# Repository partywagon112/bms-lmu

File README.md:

# Battery Management System - Local Measurement Unit

Final Year Research Project (FYRP) by Ethan Suter and Patrick Curtain to design a battery management system for an electric solar vehicle.

The Local Measurement Unit (LMU) is used to relay information about the cells to the Central Management Unit (CMU) that will they respond with balance target values for the LMU to act on. The LMU interconnects to the cell stack with the use of a terminal board, contained within the same repository. 

The LMU features an LTC6811 to monitor the cells, with two LTC3300 to actively balance the stack. These connect through multiple isolated SPI interfaces, to a microcontroller that is used to preprocess the data into a simpler form for the CMU to decypher.

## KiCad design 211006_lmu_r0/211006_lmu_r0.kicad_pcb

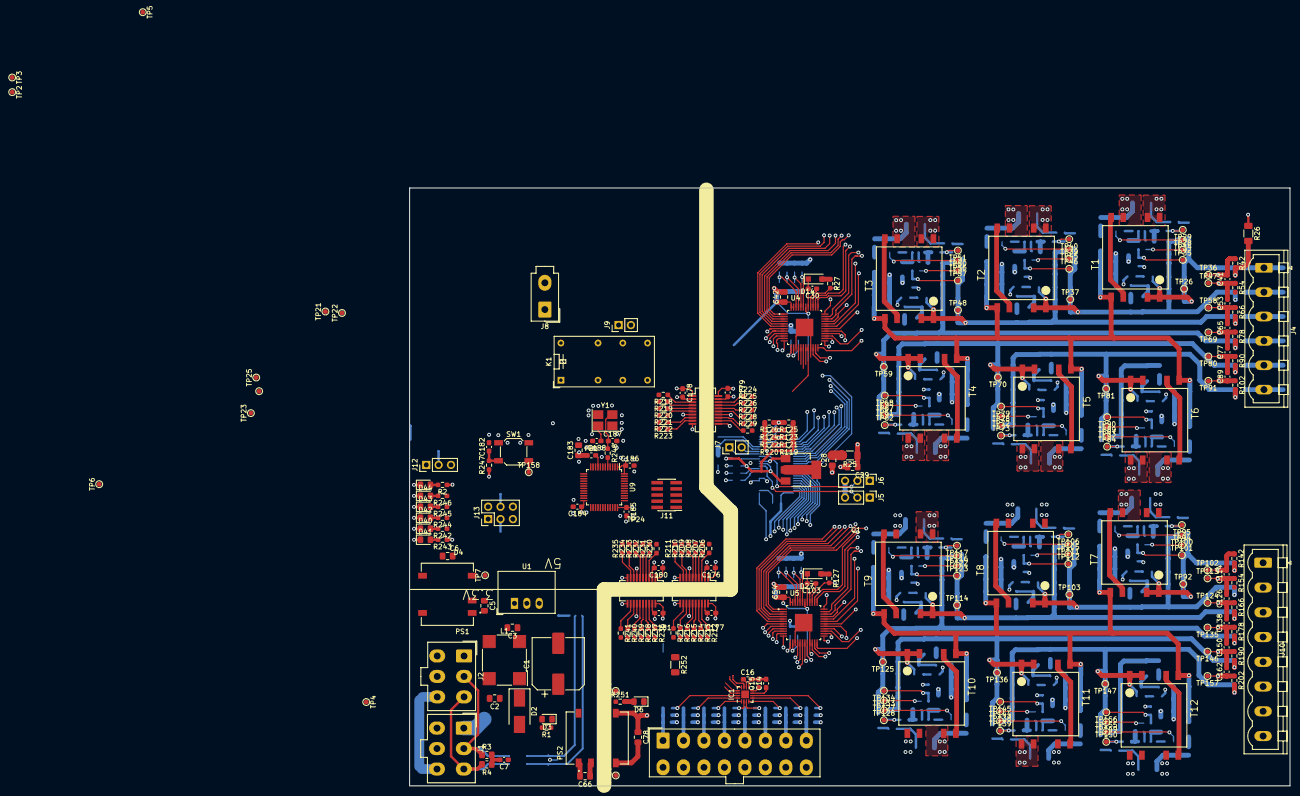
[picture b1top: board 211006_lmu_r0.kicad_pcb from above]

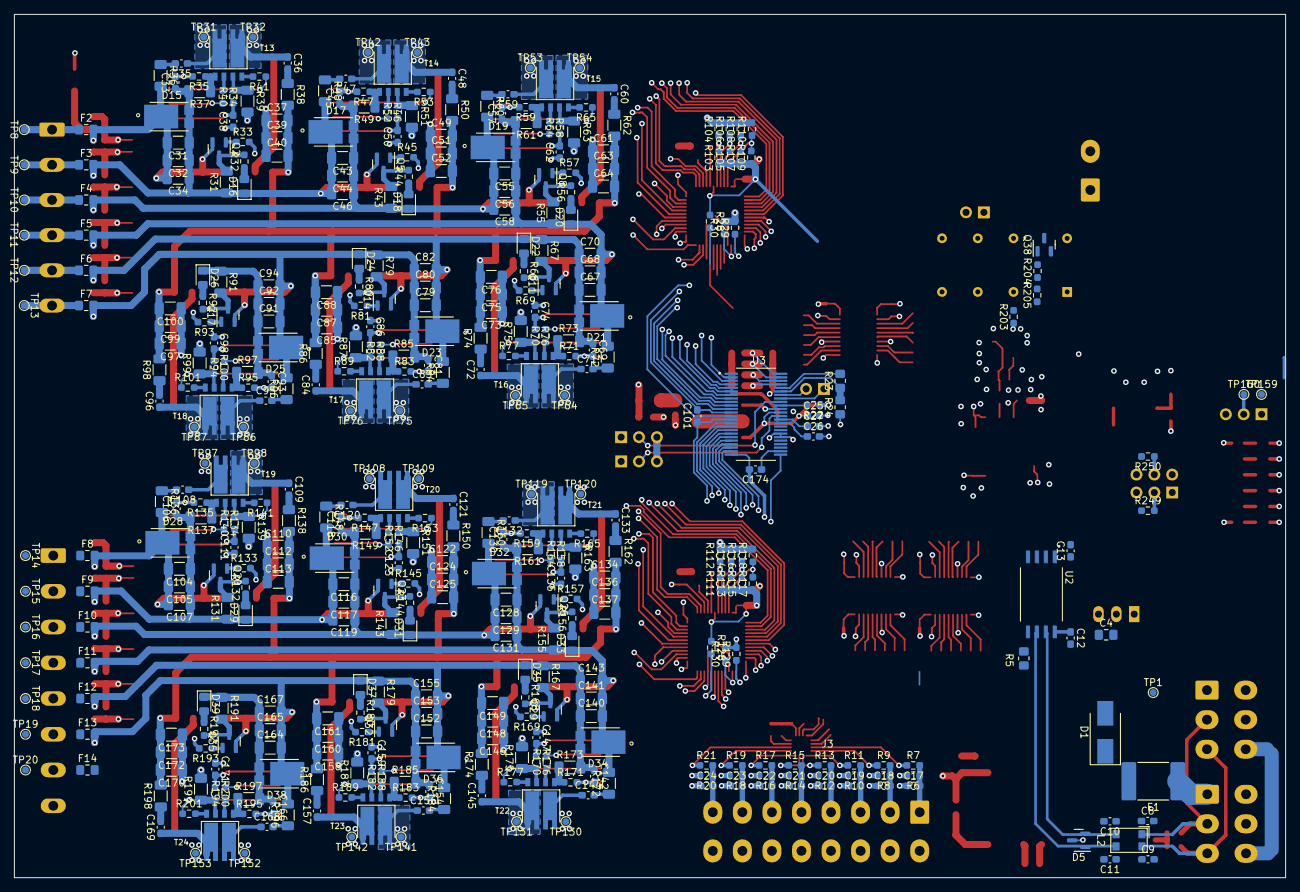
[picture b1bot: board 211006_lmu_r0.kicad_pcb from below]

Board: 4 copper layers, 180.7 x 122.7 mm, 678 parts (427 on the bottom side), 408 nets.

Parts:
C1: 220uF; CP_Elec_10x12.5
C2, C3: 10uF; C_0805_2012Metric_Pad1.18x1.45mm_HandSolder
C4, C6, C78: 22uF; C_0805_2012Metric_Pad1.18x1.45mm_HandSolder
C5, C28, C29, C66: 100nF; C_0805_2012Metric_Pad1.18x1.45mm_HandSolder
C7, C17, C18, C19, C20, C21, C22, C23, C24, C41, C53, C65, C77, C89, C101, C114, C126, C138, C150, C162, C174, C182: 10nF; C_0603_1608Metric_Pad1.08x0.95mm_HandSolder
C8, C9, C10, C11: DNP 10pF; C_0603_1608Metric_Pad1.08x0.95mm_HandSolder
C12, C13, C25, C26, C27, C30, C103, C176, C177, C178, C179, C180, C181, C184, C185, C186: 100nF; C_0603_1608Metric_Pad1.08x0.95mm_HandSolder
C14, C15, C16: 1uF; C_0603_1608Metric_Pad1.08x0.95mm_HandSolder
C31, C32, C34, C37, C39, C40, C43, C44, C46, C49, C51, C52, C55, C56, C58, C61, C63, C64, C67, C68, C70, C73, C75, C76, C79, C80, C82, C85, C87, C88, C91, C92, C94, C97, C99, C100, C104, C105, C107, C110, C112, C113, C116, C117, C119, C122, C124, C125, C128, C129, C131, C134, C136, C137, C140, C141, C143, C146, C148, C149, C152, C153, C155, C158, C160, C161, C164, C165, C167, C170, C172, C173: 100uF; C_1206_3216Metric_Pad1.33x1.80mm_HandSolder
C33, C45, C57, C69, C81, C93, C106, C118, C130, C142, C154, C166: 2.2nF; C_0603_1608Metric_Pad1.08x0.95mm_HandSolder
C35, C36, C38, C47, C48, C50, C59, C60, C62, C71, C72, C74, C83, C84, C86, C95, C96, C98, C108, C109, C111, C120, C121, C123, C132, C133, C135, C144, C145, C147, C156, C157, C159, C168, C169, C171: 470pF; C_0603_1608Metric_Pad1.08x0.95mm_HandSolder
C42, C54: 1u; C_0805_2012Metric_Pad1.18x1.45mm_HandSolder
C183: 1uF; C_0805_2012Metric_Pad1.18x1.45mm_HandSolder
C187, C188: 22p; C_0603_1608Metric_Pad1.08x0.95mm_HandSolder
D1: 1SMB5942B-13; D_SMB_Handsoldering
D2: SD560BTR; D_SMB_Handsoldering
D3, D4, D6, D16, D18, D20, D22, D24, D26, D29, D31, D33, D35, D37, D39, D41: LED (Red); LED_0805_2012Metric_Pad1.15x1.40mm_HandSolder
D5: NUP2105L; SOT-23
D14, D27: CMMSH2-40; D_SOD-123F
D15, D17, D19, D21, D23, D25, D28, D30, D32, D34, D36, D38: SDT15H100P5-7; DIO_SBR10U200P5-13
D40, D42: LED (Blue); LED_0805_2012Metric_Pad1.15x1.40mm_HandSolder
D43, D44: LED (Orange); LED_0805_2012Metric_Pad1.15x1.40mm_HandSolder
F1: Polyfuse 1A; Fuse_2920_7451Metric_Pad2.10x5.45mm_HandSolder
F2, F3, F4, F5, F6, F7, F8, F9, F10, F11, F12, F13, F14: Fuse; Fuse_0805_2012Metric_Pad1.15x1.40mm_HandSolder
FB1: Ferrite Bead; L_0603_1608Metric_Pad1.05x0.95mm_HandSolder
IC1: ADS7028QRTERQ1; WQFN-16-1EP_3x3mm_P0.5mm_EP1.6x1.6mm
J1, J2: Conn_02x03_Odd_Even; Molex_Mini-Fit_Jr_5566-06A_2x03_P4.20mm_Vertical
J3: Conn_02x08_Odd_Even; Molex_Mini-Fit_Jr_5566-16A_2x08_P4.20mm_Vertical
J4: UPPER_BANK; PhoenixContact_MSTBVA_2,5_6-G_1x06_P5.00mm_Vertical
J5, J6, J12: Conn_01x03; PinHeader_1x03_P2.54mm_Vertical
J7, J9: Conn_01x02; PinHeader_1x02_P2.54mm_Vertical
J8: Conn_01x02; Molex_Mini-Fit_Jr_5566-02A_2x01_P4.20mm_Vertical
J10: LOWER_BANK; PhoenixContact_MSTBVA_2,5_8-G-5,08_1x08_P5.08mm_Vertical
J11: Conn_ARM_JTAG_SWD_10; PinHeader_2x05_P1.27mm_Vertical_SMD
J13: Conn_02x03_Odd_Even; PinHeader_2x03_P2.54mm_Vertical
K1: G5V-2 DC-3; Relay_DPDT_Omron_G5V-2
L1: 744272121; L_CommonModeChoke_Wuerth_WE-SL5
L2: 0ZCF0100AF2A; L_CommonModeChoke_Coilcraft_1812CAN
PS1: R2S-053.3; CONV_R2S-053.3
PS2: R2S-0505; CONV_R2S-0505
Q1: CZT5551; SOT-223-3_TabPin2
Q2, Q5, Q8, Q11, Q14, Q17, Q20, Q23, Q26, Q29, Q32, Q35: BSS308PE; SOT-23
Q38: BC817; SOT-23
R1, R2, R242, R243, R244, R245, R246, R251: 2.2kR; R_0603_1608Metric_Pad0.98x0.95mm_HandSolder
R3, R4: 60R; R_0805_2012Metric_Pad1.20x1.40mm_HandSolder
R5: 0R; R_0805_2012Metric_Pad1.20x1.40mm_HandSolder
R6, R8, R10, R12, R14, R16, R18, R20, R204: 10kR; R_0603_1608Metric_Pad0.98x0.95mm_HandSolder
R7, R9, R11, R13, R15, R17, R19, R21, R203, R205, R206, R207, R208, R209, R210, R211, R212, R213, R214, R215, R216, R217, R218, R219, R220, R221, R222, R223, R224, R225, R226, R227, R228, R229, R230, R231, R232, R233, R234, R235, R236, R237, R238, R239, R240, R241, R247, R249, R250: 50kR; R_0603_1608Metric_Pad0.98x0.95mm_HandSolder
R22, R28, R128: 1MR; R_0603_1608Metric_Pad0.98x0.95mm_HandSolder
R23, R24: DNP; R_0805_2012Metric_Pad1.20x1.40mm_HandSolder
R25, R26: 100R; R_1206_3216Metric_Pad1.30x1.75mm_HandSolder
R27, R127: 6.81R; R_0603_1608Metric_Pad0.98x0.95mm_HandSolder
R29, R129: 23.7kR; R_0603_1608Metric_Pad0.98x0.95mm_HandSolder
R30, R130: 33.2kR; R_0603_1608Metric_Pad0.98x0.95mm_HandSolder
R31, R43, R55, R67, R79, R91, R131, R143, R155, R167, R179, R191: 330R; R_1206_3216Metric_Pad1.30x1.75mm_HandSolder
R32, R44, R56, R68, R80, R92, R132, R144, R156, R168, R180, R192: 470R; R_0603_1608Metric_Pad0.98x0.95mm_HandSolder
R33, R45, R57, R69, R81, R93, R133, R145, R157, R169, R181, R193: 3.3kR; R_0603_1608Metric_Pad0.98x0.95mm_HandSolder
R34, R41, R46, R53, R58, R65, R70, R77, R82, R89, R94, R101, R134, R141, R146, R153, R158, R165, R170, R177, R182, R189, R194, R201: 5.1R; R_0603_1608Metric_Pad0.98x0.95mm_HandSolder
R35, R40, R47, R52, R59, R64, R71, R76, R83, R88, R95, R100, R135, R140, R147, R152, R159, R164, R171, R176, R183, R188, R195, R200: 20R; R_0603_1608Metric_Pad0.98x0.95mm_HandSolder
R36, R38, R48, R50, R60, R62, R72, R74, R84, R86, R96, R98, R136, R138, R148, R150, R160, R162, R172, R174, R184, R186, R196, R198: 20R; R_1206_3216Metric_Pad1.30x1.75mm_HandSolder
R37, R39, R49, R51, R61, R63, R73, R75, R85, R87, R97, R99, R137, R139, R149, R151, R161, R163, R173, R175, R185, R187, R197, R199: 25mR; R_1206_3216Metric_Pad1.30x1.75mm_HandSolder
R42, R54, R66, R78, R90, R102, R142, R154, R166, R178, R190, R202: 100R; R_0603_1608Metric_Pad0.98x0.95mm_HandSolder
R103, R104, R105, R106, R107, R108, R109, R110, R111, R112, R113, R114, R115, R116, R117, R118, R119, R120, R121, R122, R123, R124, R125, R126: DNP 50k; R_0603_1608Metric_Pad0.98x0.95mm_HandSolder
R248: 0; R_0603_1608Metric_Pad0.98x0.95mm_HandSolder
R252: 0R DNP; R_1206_3216Metric_Pad1.30x1.75mm_HandSolder
SW1: SW_Push; SW_SPST_SKQG_WithStem
T1, T2, T3, T4, T5, T6, T7, T8, T9, T10, T11, T12: 750312504; EP13_SMT_H_8PIN_(750312504)
T13, T14, T15, T16, T17, T18, T19, T20, T21, T22, T23, T24: BUK9K13-60EX; SOT1205
TP1, TP2, TP3, TP4, TP5, TP6, TP7, TP8, TP9, TP10, TP11, TP12, TP13, TP14, TP15, TP16, TP17, TP18, TP19, TP20, TP21, TP22, TP23, TP24, TP25, TP26, TP28, TP29, TP30, TP31, TP32, TP33, TP34, TP35, TP36, TP37, TP39, TP40, TP42, TP43, TP45, TP46, TP47, TP48, TP50, TP51, TP53, TP54, TP56, TP57, TP58, TP59, TP61, TP62, TP64, TP65, TP67, TP68, TP69, TP70, TP72, TP73, TP75, TP76, TP78, TP79, TP80, TP81, TP83, TP84, TP86, TP87, TP89, TP90, TP91, TP92, TP94, TP95, TP97, TP98, TP100, TP101, TP102, TP103, TP105, TP106, TP108, TP109, TP111, TP112, TP113, TP114, TP116, TP117, TP119, TP120, TP122, TP123, TP124, TP125, TP127, TP128, TP130, TP131, TP133, TP134, TP135, TP136, TP138, TP139, TP141, TP142, TP144, TP145, TP146, TP147, TP149, TP150, TP152, TP153, TP155, TP156, TP157, TP158, TP159, TP160: TestPoint; TestPoint_Pad_D1.0mm
U1: R-78C5.0-1.0; Converter_DCDC_RECOM_R-78E-0.5_THT
U2: ISO1042DWVR; SOIC127P1150X280-8N
U3: LTC6811HG-2#PBF; SOP50P780X200-48N
U4, U5: LTC3300ILXE-2#PBF; QFP50P900X900X160-49N
U6, U7, U8: ADuM7641A; QSOP-20_3.9x8.7mm_P0.635mm
U9: STM32F103C8Tx; LQFP-48_7x7mm_P0.5mm
Y1: Crystal_GND24; Crystal_SMD_3225-4Pin_3.2x2.5mm_HandSoldering

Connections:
+3V3_ISO: C6.1, C13.1, C176.1, C178.1, C180.1, C183.1, C184.1, C185.1, C186.1, FB1.1, J11.1 (VTref), J13.1, J13.2, K1.1, K1.8, PS1.5 (+VOUT), R2.1, R243.1, R247.1, TP6.1, U2.1 (VCC1), U6.1 (VDD1A), U6.7 (VDD1B), U7.1 (VDD1A), U7.7 (VDD1B), U8.1 (VDD1A), U8.7 (VDD1B), U9.1 (VBAT), U9.24 (VDD), U9.36 (VDD), U9.48 (VDD)
+5V: C4.1, C5.1, C12.1, C66.1, PS1.2 (+VIN), PS2.2 (+VIN), R1.1, U1.3 (OUT), U2.8 (VCC2)
+5V_HV: C16.1, C78.1, C177.1, IC1.10 (DVDD), PS2.5 (+VOUT), R6.2, R8.2, R10.2, R12.2, R14.2, R16.2, R18.2, R20.2, R251.1, R252.2, TP30.1, U6.14 (VDD2B), U6.20 (VDD2A)
/Balance Interface/C0: C174.1, U3.26 (C0)
/Balance Interface/C1: C162.1, C174.2, R202.1, TP157.1, U3.24 (C1), U5.24 (C1)
/Balance Interface/C2: C150.1, C162.2, R190.1, TP146.1, U3.22 (C2), U5.27 (C2)
/Balance Interface/C3: C138.1, C150.2, R178.1, TP135.1, U3.20 (C3), U5.30 (C3)
/Balance Interface/C4: C126.1, C138.2, R166.1, TP124.1, U3.18 (C4), U5.33 (C4)
/Balance Interface/C5: C114.1, C126.2, R154.1, TP113.1, U3.16 (C5), U5.36 (C5)
/Balance Interface/C6: C101.1, C114.2, R127.2, R142.1, TP102.1, U3.14 (C6), U5.39 (C6)
/Balance Interface/C7: C89.1, C101.2, R102.1, TP91.1, U3.12 (C7), U4.24 (C1)
/Balance Interface/C8: C77.1, C89.2, R90.1, TP80.1, U3.10 (C8), U4.27 (C2)
/Balance Interface/C9: C65.1, C77.2, R78.1, TP69.1, U3.8 (C9), U4.30 (C3)
/Balance Interface/C10: C53.1, C65.2, R66.1, TP58.1, U3.6 (C10), U4.33 (C4)
/Balance Interface/C11: C41.1, C53.2, R54.1, TP47.1, U3.4 (C11), U4.36 (C5)
/Balance Interface/C12: C41.2, R27.2, R42.1, TP36.1, U3.2 (C12), U4.39 (C6)
/Balance Interface/CS: J7.1, R213.2, U3.41 (CSB/IMA)
/Balance Interface/DRIVE: Q1.1 (B), TP24.1, U3.38 (DRIVE)
/Balance Interface/DTEN: J5.2, U3.36 (DTEN)
/Balance Interface/IBIAS: IC1.12 (SDO), R23.2, R216.2, TP21.1, U3.44 (SDO/IBIAS)
/Balance Interface/ICMP: IC1.14 (SDI), R23.1, R24.2, R217.2, TP22.1, U3.43 (SDI/ICMP)
/Balance Interface/ISOMD: J6.2, U3.40 (ISOMD)
/Balance Interface/LOWER_ADDRESS/A0: R111.2, R112.1, U5.43 (A0)
/Balance Interface/LOWER_ADDRESS/A1: R113.2, R114.1, U5.44 (A1)
/Balance Interface/LOWER_ADDRESS/A2: R115.2, R116.1, U5.45 (A2)
/Balance Interface/LOWER_ADDRESS/A3: R117.2, R118.1, U5.46 (A3)
/Balance Interface/Lower Active Balance Group/ACTIVE_TAP1: C152.1, C153.1, C154.1, C155.1, C164.2, C165.2, C167.2, D36.2, D36.3, D37.1 (K), D38.1, F13.2, Q35.2 (S), R179.1, R185.2, R196.2, R202.2, T12.1, T12.2, TP147.1
/Balance Interface/Lower Active Balance Group/ACTIVE_TAP2: C140.1, C141.1, C142.1, C143.1, C152.2, C153.2, C155.2, D34.2, D34.3, D35.1 (K), D36.1, F12.2, Q32.2 (S), R167.1, R173.2, R184.2, R190.2, T11.1, T11.2, TP136.1
/Balance Interface/Lower Active Balance Group/ACTIVE_TAP3: C128.1, C129.1, C130.1, C131.1, C140.2, C141.2, C143.2, D32.2, D32.3, D33.1 (K), D34.1, F11.2, Q29.2 (S), R155.1, R161.2, R172.2, R178.2, T10.1, T10.2, TP125.1
/Balance Interface/Lower Active Balance Group/ACTIVE_TAP4: C116.1, C117.1, C118.1, C119.1, C128.2, C129.2, C131.2, D30.2, D30.3, D31.1 (K), D32.1, F10.2, Q26.2 (S), R143.1, R149.2, R160.2, R166.2, T9.1, T9.2, TP114.1
/Balance Interface/Lower Active Balance Group/ACTIVE_TAP5: C104.1, C105.1, C106.1, C107.1, C116.2, C117.2, C119.2, D28.2, D28.3, D29.1 (K), D30.1, F9.2, Q23.2 (S), R131.1, R137.2, R148.2, R154.2, T8.1, T8.2, TP103.1
/Balance Interface/Lower Active Balance Group/BOOST: C110.2, C112.2, C113.2, C122.2, C124.2, C125.2, C134.2, C136.2, C137.2, C146.2, C148.2, C149.2, C158.2, C160.2, C161.2, C170.2, C172.2, C173.2, R138.2, R150.2, R162.2, R174.2, R186.2, R198.2, T7.5, T8.5, T9.5, T10.5, T11.5, T12.5
/Balance Interface/Lower Active Balance Group/PG1: R194.2, TP149.1, U5.23 (G1P)
/Balance Interface/Lower Active Balance Group/PG2: R182.2, TP138.1, U5.26 (G2P)
/Balance Interface/Lower Active Balance Group/PG3: R170.2, TP127.1, U5.29 (G3P)
/Balance Interface/Lower Active Balance Group/PG4: R158.2, TP116.1, U5.32 (G4P)
/Balance Interface/Lower Active Balance Group/PG5: R146.2, TP105.1, U5.35 (G5P)
/Balance Interface/Lower Active Balance Group/PG6: R134.2, TP94.1, U5.38 (G6P)
/Balance Interface/Lower Active Balance Group/PI1: C166.2, R195.2, TP150.1, U5.22 (I1P)
/Balance Interface/Lower Active Balance Group/PI2: C154.2, R183.2, TP139.1, U5.25 (I2P)
/Balance Interface/Lower Active Balance Group/PI3: C142.2, R171.2, TP128.1, U5.28 (I3P)
/Balance Interface/Lower Active Balance Group/PI4: C130.2, R159.2, TP117.1, U5.31 (I4P)
/Balance Interface/Lower Active Balance Group/PI5: C118.2, R147.2, TP106.1, U5.34 (I5P)
/Balance Interface/Lower Active Balance Group/PI6: C106.2, R135.2, TP95.1, U5.37 (I6P)
/Balance Interface/Lower Active Balance Group/RTONP: R130.1, U5.14 (RTONP)
/Balance Interface/Lower Active Balance Group/RTONS: R129.1, U5.13 (RTONS)
/Balance Interface/Lower Active Balance Group/SG1: R201.1, TP155.1, U5.11 (G1S)
/Balance Interface/Lower Active Balance Group/SG2: R189.1, TP144.1, U5.9 (G2S)
/Balance Interface/Lower Active Balance Group/SG3: R177.1, TP133.1, U5.7 (G3S)
/Balance Interface/Lower Active Balance Group/SG4: R165.1, TP122.1, U5.5 (G4S)
/Balance Interface/Lower Active Balance Group/SG5: R153.1, TP111.1, U5.3 (G5S)
/Balance Interface/Lower Active Balance Group/SG6: R141.1, TP100.1, U5.1 (G6S)
/Balance Interface/Lower Active Balance Group/SI1: C171.2, R200.1, TP156.1, U5.12 (I1S)
/Balance Interface/Lower Active Balance Group/SI2: C159.2, R188.1, TP145.1, U5.10 (I2S)
/Balance Interface/Lower Active Balance Group/SI3: C147.2, R176.1, TP134.1, U5.8 (I3S)
/Balance Interface/Lower Active Balance Group/SI4: C135.2, R164.1, TP123.1, U5.6 (I4S)
/Balance Interface/Lower Active Balance Group/SI5: C123.2, R152.1, TP112.1, U5.4 (I5S)
/Balance Interface/Lower Active Balance Group/SI6: C111.2, R140.1, TP101.1, U5.2 (I6S)
/Balance Interface/PASSIVE_ADDRESS/A0: R119.2, R120.1, U3.45 (A0)
/Balance Interface/PASSIVE_ADDRESS/A1: R121.2, R122.1, U3.46 (A1)
/Balance Interface/PASSIVE_ADDRESS/A2: R123.2, R124.1, U3.47 (A2)
/Balance Interface/PASSIVE_ADDRESS/A3: R125.2, R126.1, U3.48 (A3)
/Balance Interface/S1: R193.2, U3.25 (S1)
/Balance Interface/S2: R181.2, U3.23 (S2)
/Balance Interface/S3: R169.2, U3.21 (S3)
/Balance Interface/S4: R157.2, U3.19 (S4)
/Balance Interface/S5: R145.2, U3.17 (S5)
/Balance Interface/S6: R133.2, U3.15 (S6)
/Balance Interface/S7: R93.2, U3.13 (S7)
/Balance Interface/S8: R81.2, U3.11 (S8)
/Balance Interface/S9: R69.2, U3.9 (S9)
/Balance Interface/S10: R57.2, U3.7 (S10)
/Balance Interface/S11: R45.2, U3.5 (S11)
/Balance Interface/S12: R33.2, U3.3 (S12)
/Balance Interface/SCK: IC1.13 (SCLK), J7.2, R215.2, U3.42 (SCK/IPA)
/Balance Interface/SCKI_LOWER: R239.2, U5.17 (SCKI)
/Balance Interface/SCKI_UPPER: R227.2, U4.17 (SCKI)
/Balance Interface/SDI_LOWER: R241.2, U5.18 (SDI)
/Balance Interface/SDI_UPPER: R229.2, U4.18 (SDI)
/Balance Interface/SDO_LOWER: R240.2, U5.19 (SDO)
/Balance Interface/SDO_UPPER: R228.2, U4.19 (SDO)
/Balance Interface/TAP0: F14.1, J10.7, J10.8, TP20.1
/Balance Interface/TAP1: F13.1, J10.6, TP19.1
/Balance Interface/TAP2: F12.1, J10.5, TP18.1
/Balance Interface/TAP3: F11.1, J10.4, TP17.1
/Balance Interface/TAP4: F10.1, J10.3, TP16.1
/Balance Interface/TAP5: F9.1, J10.2, TP15.1
/Balance Interface/TAP6: F8.1, J10.1, TP14.1
/Balance Interface/TAP7: F7.1, J4.6, TP13.1
/Balance Interface/TAP8: F6.1, J4.5, TP12.1
/Balance Interface/TAP9: F5.1, J4.4, TP11.1
/Balance Interface/TAP10: F4.1, J4.3, TP10.1
/Balance Interface/TAP11: F3.1, J4.2, TP9.1
/Balance Interface/TAP12: F2.1, J4.1, TP8.1
/Balance Interface/UPPER_ADDRESS/A0: R103.2, R104.1, U4.43 (A0)
/Balance Interface/UPPER_ADDRESS/A1: R105.2, R106.1, U4.44 (A1)
/Balance Interface/UPPER_ADDRESS/A2: R107.2, R108.1, U4.45 (A2)
/Balance Interface/UPPER_ADDRESS/A3: R109.2, R110.1, U4.46 (A3)
/Balance Interface/Upper Active Balance Group/ACTIVE_TAP1: C79.1, C80.1, C81.1, C82.1, C91.2, C92.2, C94.2, D23.2, D23.3, D24.1 (K), D25.1, F7.2, Q17.2 (S), R79.1, R85.2, R96.2, R102.2, T6.1, T6.2, TP81.1
/Balance Interface/Upper Active Balance Group/ACTIVE_TAP2: C67.1, C68.1, C69.1, C70.1, C79.2, C80.2, C82.2, D21.2, D21.3, D22.1 (K), D23.1, F6.2, Q14.2 (S), R67.1, R73.2, R84.2, R90.2, T5.1, T5.2, TP70.1
/Balance Interface/Upper Active Balance Group/ACTIVE_TAP3: C55.1, C56.1, C57.1, C58.1, C67.2, C68.2, C70.2, D19.2, D19.3, D20.1 (K), D21.1, F5.2, Q11.2 (S), R55.1, R61.2, R72.2, R78.2, T4.1, T4.2, TP59.1
/Balance Interface/Upper Active Balance Group/ACTIVE_TAP4: C43.1, C44.1, C45.1, C46.1, C55.2, C56.2, C58.2, D17.2, D17.3, D18.1 (K), D19.1, F4.2, Q8.2 (S), R43.1, R49.2, R60.2, R66.2, T3.1, T3.2, TP48.1
/Balance Interface/Upper Active Balance Group/ACTIVE_TAP5: C31.1, C32.1, C33.1, C34.1, C43.2, C44.2, C46.2, D15.2, D15.3, D16.1 (K), D17.1, F3.2, Q5.2 (S), R31.1, R37.2, R48.2, R54.2, T2.1, T2.2, TP37.1
/Balance Interface/Upper Active Balance Group/BOOST: C37.2, C39.2, C40.2, C49.2, C51.2, C52.2, C61.2, C63.2, C64.2, C73.2, C75.2, C76.2, C85.2, C87.2, C88.2, C97.2, C99.2, C100.2, R38.2, R50.2, R62.2, R74.2, R86.2, R98.2, T1.5, T2.5, T3.5, T4.5, T5.5, T6.5
/Balance Interface/Upper Active Balance Group/PG1: R94.2, TP83.1, U4.23 (G1P)
/Balance Interface/Upper Active Balance Group/PG2: R82.2, TP72.1, U4.26 (G2P)
/Balance Interface/Upper Active Balance Group/PG3: R70.2, TP61.1, U4.29 (G3P)
/Balance Interface/Upper Active Balance Group/PG4: R58.2, TP50.1, U4.32 (G4P)
/Balance Interface/Upper Active Balance Group/PG5: R46.2, TP39.1, U4.35 (G5P)
/Balance Interface/Upper Active Balance Group/PG6: R34.2, TP28.1, U4.38 (G6P)
/Balance Interface/Upper Active Balance Group/PI1: C93.2, R95.2, TP84.1, U4.22 (I1P)
/Balance Interface/Upper Active Balance Group/PI2: C81.2, R83.2, TP73.1, U4.25 (I2P)
/Balance Interface/Upper Active Balance Group/PI3: C69.2, R71.2, TP62.1, U4.28 (I3P)
/Balance Interface/Upper Active Balance Group/PI4: C57.2, R59.2, TP51.1, U4.31 (I4P)
/Balance Interface/Upper Active Balance Group/PI5: C45.2, R47.2, TP40.1, U4.34 (I5P)
/Balance Interface/Upper Active Balance Group/PI6: C33.2, R35.2, TP29.1, U4.37 (I6P)
/Balance Interface/Upper Active Balance Group/RTONP: R30.1, U4.14 (RTONP)
/Balance Interface/Upper Active Balance Group/RTONS: R29.1, U4.13 (RTONS)
/Balance Interface/Upper Active Balance Group/SG1: R101.1, TP89.1, U4.11 (G1S)
/Balance Interface/Upper Active Balance Group/SG2: R89.1, TP78.1, U4.9 (G2S)
/Balance Interface/Upper Active Balance Group/SG3: R77.1, TP67.1, U4.7 (G3S)
/Balance Interface/Upper Active Balance Group/SG4: R65.1, TP56.1, U4.5 (G4S)
/Balance Interface/Upper Active Balance Group/SG5: R53.1, TP45.1, U4.3 (G5S)
/Balance Interface/Upper Active Balance Group/SG6: R41.1, TP34.1, U4.1 (G6S)
/Balance Interface/Upper Active Balance Group/SI1: C98.2, R100.1, TP90.1, U4.12 (I1S)
/Balance Interface/Upper Active Balance Group/SI2: C86.2, R88.1, TP79.1, U4.10 (I2S)
/Balance Interface/Upper Active Balance Group/SI3: C74.2, R76.1, TP68.1, U4.8 (I3S)
/Balance Interface/Upper Active Balance Group/SI4: C62.2, R64.1, TP57.1, U4.6 (I4S)
/Balance Interface/Upper Active Balance Group/SI5: C50.2, R52.1, TP46.1, U4.4 (I5S)
/Balance Interface/Upper Active Balance Group/SI6: C38.2, R40.1, TP35.1, U4.2 (I6S)
/Balance Interface/V+: C31.2, C32.2, C34.2, D15.1, F2.2, Q2.2 (S), R26.2, R36.2, R42.2, T1.1, T1.2, TP26.1
/Balance Interface/VREG: C25.1, J5.3, J6.3, Q1.3 (E), R22.1, R119.1, R121.1, R123.1, R125.1, R252.1, TP25.1, U3.37 (VREG)
/Balance Interface/VREG_LOWER: C54.1, C181.1, R111.1, R113.1, R115.1, R117.1, R128.1, U5.42 (BOOST), U5.48 (VREG), U8.14 (VDD2B), U8.20 (VDD2A)
/Balance Interface/VREG_UPPER: C42.1, C179.1, R28.1, R103.1, R105.1, R107.1, R109.1, U4.42 (BOOST), U4.47 (A4), U4.48 (VREG), U7.14 (VDD2B), U7.20 (VDD2A)
/Balance Interface/V_TEMP_SENSOR_REF: C26.1, U3.34 (VREF2)
/Balance Interface/WDT: R22.2, R212.2, U3.39 (WDT)
/Balance Interface/WDT_LOWER: R128.2, R236.2, U5.20 (WDT)
/Balance Interface/WDT_UPPER: R28.2, R224.2, U4.20 (WDT)
/Balance Interface/nCSBI_LOWER: R237.2, U5.16 (~CSBI)
/Balance Interface/nCSBI_UPPER: R225.2, U4.16 (~CSBI)
/CAN/CAN_PRE_N: C11.1, D5.1 (K), L2.3, U2.6 (CANL)
/CAN/CAN_PRE_P: C10.1, D5.2 (K), L2.2, U2.7 (CANH)
/CAN_N: C9.1, J1.3, J2.3, L2.4, R4.2
/CAN_P: C8.1, J1.2, J2.2, L2.1, R3.1
/CAN_S: C7.1, C8.2, C9.2, C10.2, C11.2, D5.3 (A), J1.6, J2.6, R5.2, U2.5 (GND2)
/CS_ACTIVE_LOWER: R231.2, U9.40 (PB4)
/CS_ACTIVE_UPPER: R219.2, U9.18 (PB0)
/CS_PASSIVE: R207.2, U9.11 (PA1)
/CS_TEMPERATURE: R208.2, U9.10 (PA0)
/Microcontroller/BOOT0: R249.1, U9.44 (BOOT0)
/Microcontroller/BOOT1: R250.2, U9.20 (PB2)
/Microcontroller/CAN_RX: U2.2 (RXD), U9.32 (PA11)
/Microcontroller/CAN_TX: U2.3 (TXD), U9.33 (PA12)
/Microcontroller/LED0: D41.1 (K), U9.2 (PC13)
/Microcontroller/LMS_OK: R204.1, R205.2, U9.30 (PA9)
/Microcontroller/LMS_OK_FB: R203.1, U9.29 (PA8)
/Microcontroller/NRST: C182.1, J11.10 (~RESET), R247.2, SW1.2, TP158.1, U9.7 (NRST)
/Microcontroller/RCC_OSC_IN: C187.1, R248.1, Y1.3
/Microcontroller/RCC_OSC_OUT: C188.1, U9.6 (PD1), Y1.1
/Microcontroller/SPI1_CLK: R209.2, R221.2, R233.2, U9.15 (PA5)
/Microcontroller/SPI1_MISO: R211.2, R223.2, R235.2, U9.16 (PA6)
/Microcontroller/SPI1_MOSI: R210.2, R222.2, R234.2, U9.17 (PA7)
/Microcontroller/SWCLK: J11.4 (SWDCLK/TCK), U9.37 (PA14)
/Microcontroller/SWDIO: J11.2 (SWDIO/TMS), U9.34 (PA13)
/Microcontroller/USART_RX: J12.2, TP160.1, U9.13 (PA3)
/Microcontroller/USART_TX: J12.1, TP159.1, U9.12 (PA2)
/SDN_IN: J8.2, J9.2, K1.9
/SDN_OUT: J8.1, J9.1, K1.13
/Temperature Isolation/CS1: IC1.11 (~CS), R214.2
/Temperature Sensor/TmpOut0: IC1.15 (AIN0/GPIO0), R7.1
/Temperature Sensor/TmpOut1: IC1.16 (AIN1/GPIO1), R9.1
/Temperature Sensor/TmpOut2: IC1.1 (AIN2/GPIO2), R11.1
/Temperature Sensor/TmpOut3: IC1.2 (AIN3/GPIO3), R13.1
/Temperature Sensor/TmpOut4: IC1.3 (AIN4/GPIO4), R15.1
/Temperature Sensor/TmpOut5: IC1.4 (AIN5/GPIO5), R17.1
/Temperature Sensor/TmpOut6: IC1.5 (AIN6/GPIO6), R19.1
/Temperature Sensor/TmpOut7: IC1.6 (AIN7/GPIO7), R21.1
/TmpCon0: C17.2, J3.1, R6.1, R7.2
/TmpCon1: C18.2, J3.2, R8.1, R9.2
/TmpCon2: C19.2, J3.3, R10.1, R11.2
/TmpCon3: C20.2, J3.4, R12.1, R13.2
/TmpCon4: C21.2, J3.5, R14.1, R15.2
/TmpCon5: C22.2, J3.6, R16.1, R17.2
/TmpCon6: C23.2, J3.7, R18.1, R19.2
/TmpCon7: C24.2, J3.8, R20.1, R21.2
/UPPER_GND: C37.1, C38.1, C39.1, C40.1, C42.2, C49.1, C50.1, C51.1, C52.1, C61.1, C62.1, C63.1, C64.1, C73.1, C74.1, C75.1, C76.1, C85.1, C86.1, C87.1, C88.1, C91.1, C92.1, C93.1, C94.1, C97.1, C98.1, C99.1, C100.1, C104.2, C105.2, C107.2, C179.2, D25.2, D25.3, D26.1 (K), D28.1, F8.2, Q20.2 (S), R29.2, R30.2, R39.2, R51.2, R63.2, R75.2, R87.2, R91.1, R97.2, R99.2, R104.2, R106.2, R108.2, R110.2, R136.2, R142.2, T7.1, T7.2, TP92.1, U4.15 (CTRL), U4.21 (V-), U4.49 (V-), U7.11 (GND2), U7.19 (GND2)
/VBAT: F1.1, J1.1, J2.1, TP1.1
/VGND: C1.2, C2.2, D1.2 (A2), J1.4, J2.4, L1.4, TP2.1
/WDT_ACTIVE_LOWER: R230.2, U9.39 (PB3)
/WDT_ACTIVE_UPPER: R218.2, U9.19 (PB1)
/WDT_PASSIVE: R206.2, U9.14 (PA4)
GND: C3.2, C4.2, C5.2, C12.2, C66.2, D3.1 (K), L1.3, PS1.1 (-VIN), PS2.1 (-VIN), R5.1, TP5.1, U1.2 (GND)
GND_HV: C14.2, C15.2, C16.2, C17.1, C18.1, C19.1, C20.1, C21.1, C22.1, C23.1, C24.1, C25.2, C26.2, C27.2, C28.1, C29.2, C54.2, C78.2, C110.1, C111.1, C112.1, C113.1, C122.1, C123.1, C124.1, C125.1, C134.1, C135.1, C136.1, C137.1, C146.1, C147.1, C148.1, C149.1, C158.1, C159.1, C160.1, C161.1, C164.1, C165.1, C166.1, C167.1, C170.1, C171.1, C172.1, C173.1, C177.2, C181.2, D6.1 (K), D38.2, D38.3, D39.1 (K), F14.2, IC1.9 (GND), IC1.17 (EP), J3.9, J3.10, J3.11, J3.12, J3.13, J3.14, J3.15, J3.16, J5.1, J6.1, PS2.4 (-VOUT), R24.1, R112.2, R114.2, R116.2, R118.2, R120.2, R122.2, R124.2, R126.2, R129.2, R130.2, R139.2, R151.2, R163.2, R175.2, R187.2, R191.1, R197.2, R199.2, TP33.1, U3.30 (V-), U3.31 (V-), U5.15 (CTRL), U5.21 (V-), U5.47 (A4), U5.49 (V-), U6.11 (GND2), U6.19 (GND2), U8.11 (GND2), U8.19 (GND2)
GND_ISO: C6.2, C13.2, C176.2, C178.2, C180.2, C182.2, C183.2, C184.2, C185.2, C186.2, C187.2, C188.2, D4.1 (K), D40.1 (K), D42.1 (K), D43.1 (K), D44.1 (K), J11.3 (GND), J11.5 (GND), J11.9 (GNDDetect), J12.3, J13.5, J13.6, K1.6, PS1.4 (-VOUT), Q38.2 (E), R205.1, SW1.1, TP7.1, U2.4 (GND1), U6.2 (GND1), U6.10 (GND1), U7.2 (GND1), U7.10 (GND1), U8.2 (GND1), U8.10 (GND1), U9.8 (VSSA), U9.23 (VSS), U9.35 (VSS), U9.47 (VSS), Y1.2, Y1.4
unnamed: C1.1, C2.1, D2.1 (K), L1.1, TP3.1
unnamed: C3.1, L1.2, TP4.1, U1.1 (IN)
unnamed: C7.2, R3.2, R4.1
unnamed: C14.1, IC1.7 (AVDD)
unnamed: C15.1, IC1.8 (DECAP)
unnamed: C27.1, U3.35 (VREF1)
unnamed: C28.2, Q1.2 (C), R25.2
unnamed: C29.1, R25.1, R26.1, TP23.1, U3.1 (V+)
unnamed: C30.1, U4.40 (BOOSTP)
unnamed: C30.2, D14.1 (K), U4.41 (BOOSTN)
unnamed: C35.1, T1.9, T1.10, T13.7, T13.8, T13.S1, TP31.1
unnamed: C35.2, R36.1
unnamed: C36.1, T1.7, T13.5, T13.6, T13.S2, TP32.1
unnamed: C36.2, R38.1
unnamed: C47.1, T2.9, T2.10, T14.7, T14.8, T14.S1, TP42.1
unnamed: C47.2, R48.1
unnamed: C48.1, T2.7, T14.5, T14.6, T14.S2, TP43.1
unnamed: C48.2, R50.1
unnamed: C59.1, T3.9, T3.10, T15.7, T15.8, T15.S1, TP53.1
unnamed: C59.2, R60.1
unnamed: C60.1, T3.7, T15.5, T15.6, T15.S2, TP54.1
unnamed: C60.2, R62.1
unnamed: C71.1, T4.9, T4.10, T16.7, T16.8, T16.S1, TP64.1
unnamed: C71.2, R72.1
unnamed: C72.1, T4.7, T16.5, T16.6, T16.S2, TP65.1
unnamed: C72.2, R74.1
unnamed: C83.1, T5.9, T5.10, T17.7, T17.8, T17.S1, TP75.1
unnamed: C83.2, R84.1
unnamed: C84.1, T5.7, T17.5, T17.6, T17.S2, TP76.1
unnamed: C84.2, R86.1
unnamed: C95.1, T6.9, T6.10, T18.7, T18.8, T18.S1, TP86.1
unnamed: C95.2, R96.1
unnamed: C96.1, T6.7, T18.5, T18.6, T18.S2, TP87.1
unnamed: C96.2, R98.1
unnamed: C103.1, U5.40 (BOOSTP)
unnamed: C103.2, D27.1 (K), U5.41 (BOOSTN)
unnamed: C108.1, T7.9, T7.10, T19.7, T19.8, T19.S1, TP97.1
unnamed: C108.2, R136.1
unnamed: C109.1, T7.7, T19.5, T19.6, T19.S2, TP98.1
unnamed: C109.2, R138.1
unnamed: C120.1, T8.9, T8.10, T20.7, T20.8, T20.S1, TP108.1
unnamed: C120.2, R148.1
unnamed: C121.1, T8.7, T20.5, T20.6, T20.S2, TP109.1
unnamed: C121.2, R150.1
unnamed: C132.1, T9.9, T9.10, T21.7, T21.8, T21.S1, TP119.1
unnamed: C132.2, R160.1
unnamed: C133.1, T9.7, T21.5, T21.6, T21.S2, TP120.1
unnamed: C133.2, R162.1
unnamed: C144.1, T10.9, T10.10, T22.7, T22.8, T22.S1, TP130.1
unnamed: C144.2, R172.1
unnamed: C145.1, T10.7, T22.5, T22.6, T22.S2, TP131.1
unnamed: C145.2, R174.1
unnamed: C156.1, T11.9, T11.10, T23.7, T23.8, T23.S1, TP141.1
unnamed: C156.2, R184.1
unnamed: C157.1, T11.7, T23.5, T23.6, T23.S2, TP142.1
unnamed: C157.2, R186.1
unnamed: C168.1, T12.9, T12.10, T24.7, T24.8, T24.S1, TP152.1
unnamed: C168.2, R196.1
unnamed: C169.1, T12.7, T24.5, T24.6, T24.S2, TP153.1
unnamed: C169.2, R198.1
unnamed: D1.1 (A1), D2.2 (A), F1.2
unnamed: D3.2 (A), R1.2
unnamed: D4.2 (A), R2.2
unnamed: D6.2 (A), R251.2
unnamed: D14.2 (A), R27.1
unnamed: D16.2 (A), R32.1
unnamed: D18.2 (A), R44.1
unnamed: D20.2 (A), R56.1
unnamed: D22.2 (A), R68.1
unnamed: D24.2 (A), R80.1
unnamed: D26.2 (A), R92.1
unnamed: D27.2 (A), R127.1
unnamed: D29.2 (A), R132.1
unnamed: D31.2 (A), R144.1
unnamed: D33.2 (A), R156.1
unnamed: D35.2 (A), R168.1
unnamed: D37.2 (A), R180.1
unnamed: D39.2 (A), R192.1
unnamed: D40.2 (A), R242.2
unnamed: D41.2 (A), R243.2
unnamed: D42.2 (A), R244.2
unnamed: D43.2 (A), R245.2
unnamed: D44.2 (A), R246.2
unnamed: FB1.2, U9.9 (VDDA)
unnamed: J13.3, R249.2
unnamed: J13.4, R250.1
unnamed: K1.4, R203.2
unnamed: K1.16, Q38.3 (C)
unnamed: Q2.1 (G), R33.1
unnamed: Q2.3 (D), R31.2, R32.2
unnamed: Q5.1 (G), R45.1
unnamed: Q5.3 (D), R43.2, R44.2
unnamed: Q8.1 (G), R57.1
unnamed: Q8.3 (D), R55.2, R56.2
unnamed: Q11.1 (G), R69.1
unnamed: Q11.3 (D), R67.2, R68.2
unnamed: Q14.1 (G), R81.1
unnamed: Q14.3 (D), R79.2, R80.2
unnamed: Q17.1 (G), R93.1
unnamed: Q17.3 (D), R91.2, R92.2
unnamed: Q20.1 (G), R133.1
unnamed: Q20.3 (D), R131.2, R132.2
unnamed: Q23.1 (G), R145.1
unnamed: Q23.3 (D), R143.2, R144.2
unnamed: Q26.1 (G), R157.1
unnamed: Q26.3 (D), R155.2, R156.2
unnamed: Q29.1 (G), R169.1
unnamed: Q29.3 (D), R167.2, R168.2
unnamed: Q32.1 (G), R181.1
unnamed: Q32.3 (D), R179.2, R180.2
unnamed: Q35.1 (G), R193.1
unnamed: Q35.3 (D), R191.2, R192.2
unnamed: Q38.1 (B), R204.2
unnamed: R34.1, T13.2
unnamed: R35.1, R37.1, T13.1
unnamed: R39.1, R40.2, T13.3
unnamed: R41.2, T13.4
unnamed: R46.1, T14.2
unnamed: R47.1, R49.1, T14.1
unnamed: R51.1, R52.2, T14.3
unnamed: R53.2, T14.4
unnamed: R58.1, T15.2
unnamed: R59.1, R61.1, T15.1
unnamed: R63.1, R64.2, T15.3
unnamed: R65.2, T15.4
unnamed: R70.1, T16.2
unnamed: R71.1, R73.1, T16.1
unnamed: R75.1, R76.2, T16.3
unnamed: R77.2, T16.4
unnamed: R82.1, T17.2
unnamed: R83.1, R85.1, T17.1
unnamed: R87.1, R88.2, T17.3
unnamed: R89.2, T17.4
unnamed: R94.1, T18.2
unnamed: R95.1, R97.1, T18.1
unnamed: R99.1, R100.2, T18.3
unnamed: R101.2, T18.4
unnamed: R134.1, T19.2
unnamed: R135.1, R137.1, T19.1
unnamed: R139.1, R140.2, T19.3
unnamed: R141.2, T19.4
unnamed: R146.1, T20.2
unnamed: R147.1, R149.1, T20.1
unnamed: R151.1, R152.2, T20.3
unnamed: R153.2, T20.4
unnamed: R158.1, T21.2
unnamed: R159.1, R161.1, T21.1
unnamed: R163.1, R164.2, T21.3
unnamed: R165.2, T21.4
unnamed: R170.1, T22.2
unnamed: R171.1, R173.1, T22.1
unnamed: R175.1, R176.2, T22.3
unnamed: R177.2, T22.4
unnamed: R182.1, T23.2
unnamed: R183.1, R185.1, T23.1
unnamed: R187.1, R188.2, T23.3
unnamed: R189.2, T23.4
unnamed: R194.1, T24.2
unnamed: R195.1, R197.1, T24.1
unnamed: R199.1, R200.2, T24.3
unnamed: R201.2, T24.4
unnamed: R206.1, U6.3 (VIA)
unnamed: R207.1, U6.4 (VIB)
unnamed: R208.1, U6.5 (VIC)
unnamed: R209.1, U6.6 (VID)
unnamed: R210.1, U6.8 (VOE)
unnamed: R211.1, U6.9 (VIF)
unnamed: R212.1, U6.18 (VOA)
unnamed: R213.1, U6.17 (VOB)
unnamed: R214.1, U6.16 (VOC)
unnamed: R215.1, U6.15 (VOD)
unnamed: R216.1, U6.13 (VIE)
unnamed: R217.1, U6.12 (VOF)
unnamed: R218.1, U7.3 (VIA)
unnamed: R219.1, U7.4 (VIB)
unnamed: R220.1, U7.5 (VIC)
unnamed: R221.1, U7.6 (VID)
unnamed: R222.1, U7.8 (VOE)
unnamed: R223.1, U7.9 (VIF)
unnamed: R224.1, U7.18 (VOA)
unnamed: R225.1, U7.17 (VOB)
unnamed: R226.1, U7.16 (VOC)
unnamed: R227.1, U7.15 (VOD)
unnamed: R228.1, U7.13 (VIE)
unnamed: R229.1, U7.12 (VOF)
unnamed: R230.1, U8.3 (VIA)
unnamed: R231.1, U8.4 (VIB)
unnamed: R232.1, U8.5 (VIC)
unnamed: R233.1, U8.6 (VID)
unnamed: R234.1, U8.8 (VOE)
unnamed: R235.1, U8.9 (VIF)
unnamed: R236.1, U8.18 (VOA)
unnamed: R237.1, U8.17 (VOB)
unnamed: R238.1, U8.16 (VOC)
unnamed: R239.1, U8.15 (VOD)
unnamed: R240.1, U8.13 (VIE)
unnamed: R241.1, U8.12 (VOF)
unnamed: R242.1, U9.41 (PB5)
unnamed: R244.1, U9.42 (PB6)
unnamed: R245.1, U9.43 (PB7)
unnamed: R246.1, U9.45 (PB8)
unnamed: R248.2, U9.5 (PD0)
unnamed: T1.4, T1.6
unnamed: T2.4, T2.6
unnamed: T3.4, T3.6
unnamed: T4.4, T4.6
unnamed: T5.4, T5.6
unnamed: T6.4, T6.6
unnamed: T7.4, T7.6
unnamed: T8.4, T8.6
unnamed: T9.4, T9.6
unnamed: T10.4, T10.6
unnamed: T11.4, T11.6
unnamed: T12.4, T12.6

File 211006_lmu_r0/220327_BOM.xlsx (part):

Item | Qty | Reference(s) | Value | LibPart | Footprint | Datasheet | AVAILABILITY | Description | Height | MANUFACTURER | MAXIMUM_PACKAGE_HEIGHT | MP | Manufacturer | Mouser Part Number | Mouser Price/Stock | Mouser URL | PACKAGE | PARTREV | PRICE | Part Number | SNAPEDA_PACKAGE_ID | STANDARD | Voltage
1 | 1 | C1 | 220uF | Device:C_Polarized_US | Capacitor_SMD:CP_Elec_10x12.5 | ~ |  |  |  |  |  |  | Vishay | 594-MAL214699106E3 |  | https://au.mouser.com/ProductDetail/Vishay-BC-Components/MAL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 |  |  |  | MAL214699106E3
2 | 2 | C2, C3 | 10uF | Device:C | Capacitor_SMD:C_0805_2012Metric_Pad1.18x1.45mm_HandSolder | ~ |  |  |  |  |  |  |  |  |  |  |  |  |  | -
3 | 2 | C4, C6 | 22uF | Device:C | Capacitor_SMD:C_0805_2012Metric_Pad1.18x1.45mm_HandSolder | ~ |  |  |  |  |  |  |  |  |  |  |  |  |  | -
4 | 17 | C5, C12, C13, C25, C26, C27, C30, C103, C176, C177, C178, C179, C180, C181, C18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 | 100nF | Device:C | Capacitor_SMD:C_0603_1608Metric_Pad1.08x0.95mm_HandSolder | ~ |  |  |  |  |  |  |  |  |  |  |  |  |  | -
5 | 22 | C7, C17, C18, C19, C20, C21, C22, C23, C24, C41, C53, C65, C77, C89, C101, C114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 | 10nF | Device:C | Capacitor_SMD:C_0603_1608Metric_Pad1.08x0.95mm_HandSolder | ~ |  |  |  |  |  |  |  |  |  |  |  |  |  | -
6 | 4 | C8, C9, C10, C11 | DNP 10pF | Device:C | Capacitor_SMD:C_0603_1608Metric_Pad1.08x0.95mm_HandSolder | ~ |  |  |  |  |  |  |  |  |  |  |  |  |  | -
7 | 3 | C14, C15, C16 | 1uF | Device:C | Capacitor_SMD:C_0603_1608Metric_Pad1.08x0.95mm_HandSolder | ~ |  |  |  |  |  |  |  |  |  |  |  |  |  | -
8 | 2 | C28, C29 | 100nF | Device:C | Capacitor_SMD:C_0805_2012Metric_Pad1.18x1.45mm_HandSolder | ~ |  |  |  |  |  |  |  |  |  |  |  |  |  | -
9 | 72 | C31, C32, C34, C37, C39, C40, C43, C44, C46, C49, C51, C52, C55, C56, C58, C61,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 | 100uF | Device:C | Capacitor_SMD:C_1206_3216Metric_Pad1.33x1.80mm_HandSolder | ~ |  |  |  |  |  |  |  |  |  |  |  |  |  |  |  |  | 100V
10 | 12 | C33, C45, C57, C69, C81, C93, C106, C118, C130, C142, C154, C166 | 2.2nF | Device:C | Capacitor_SMD:C_0603_1608Metric_Pad1.08x0.95mm_HandSolder | ~ |  |  |  |  |  |  |  |  |  |  |  |  |  | -
11 | 36 | C35, C36, C38, C47, C48, C50, C59, C60, C62, C71, C72, C74, C83, C84, C86, C95,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 | 470pF | Device:C | Capacitor_SMD:C_0603_1608Metric_Pad1.08x0.95mm_HandSolder | ~ |  |  |  |  |  |  |  |  |  |  |  |  |  |  |  |  | 100V
12 | 12 | C42, C54, C66, C78, C90, C102, C115, C127, C139, C151, C163, C175 | DNP 10nF | Device:C | Capacitor_SMD:C_0805_2012Metric_Pad1.18x1.45mm_HandSolder | ~ |  |  |  |  |  |  |  |  |  |  |  |  |  |  |  |  | 100V
13 | 1 | C183 | 1uF | Device:C | Capacitor_SMD:C_0805_2012Metric_Pad1.18x1.45mm_HandSolder | ~ |  |  |  |  |  |  |  |  |  |  |  |  |  | -
14 | 1 | D1 | 1SMB5942B-13 | Device:D_TVS | Diode_SMD:D_SMB_Handsoldering | ~ |  |  |  |  |  |  | Diodes Inc | 621-1SMB5942B-13 |  | https://au.mouser.com/ProductDetail/Diodes-Incorporated/1SMB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 |  |  |  | 1SMB5942B-13
15 | 1 | D2 | SD560BTR | Device:D | Diode_SMD:D_SMB_Handsoldering | ~ |  |  |  |  |  |  | SMC Diode Solutions | NOT AVAILABLE! |  | NOT AVAILABLE! |  |  |  | SD560BTR
16 | 15 | D3, D4, D16, D18, D20, D22, D24, D26, D29, D31, D33, D35, D37, D39, D41 | LED (Red) | Device:LED | LED_SMD:LED_0805_2012Metric_Pad1.15x1.40mm_HandSolder | ~ |  |  |  |  |  |  | AMS OSRAM | 720-LSR976-NR-1 |  | https://au.mouser.com/ProductDetail/ams-OSRAM/LS-R976-NR-1-0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 |  |  |  | LS R976-NR-1-0-20-R18
17 | 1 | D5 | NUP2105L | Power_Protection:NUP2105L | Package_TO_SOT_SMD:SOT-23 | http://www.onsemi.com/pub_link/Collateral/NUP2105L-D.PDF |  |  |  |  |  |  | ON Semiconductor | 863-SZNUP2105LT1G |  | https://au.mouser.com/ProductDetail/onsemi/SZNUP2105LT1G?qs=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 |  |  |  | NUP2105L
18 | 8 | D6, D7, D8, D9, D10, D11, D12, D13 | SMAZ5V6-13-F | Device:D_Zener | Diode_SMD:D_SMA_Handsoldering | ~ |  |  |  |  |  |  | Diodes Inc | NOT AVAILABLE! |  | NOT AVAILABLE! |  |  |  | SMAZ5V6-13-F
19 | 2 | D14, D27 | CMMSH2-40 | Device:D_Schottky | Diode_SMD:D_SOD-123F | ~ |  |  |  |  |  |  | Central Semiconductor | 610-CMMSH2-40TR |  | https://au.mouser.com/ProductDetail/Central-Semiconductor/CM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 |  |  |  | CMMSH2-40
20 | 12 | D15, D17, D19, D21, D23, D25, D28, D30, D32, D34, D36, D38 | SBR10U200P5-13 | SBR10U200P5-13:SBR10U200P5-13 | DIO_SBR10U200P5-13 |  |  |  |  | Diodes Inc |  |  | Diodes Inc | NOT AVAILABLE! |  | NOT AVAILABLE! |  |  |  | SBR10U200P5-13
21 | 2 | D40, D42 | LED (Blue) | Device:LED | LED_SMD:LED_0805_2012Metric_Pad1.15x1.40mm_HandSolder | ~ |  |  |  |  |  |  | Lumex | SML-LX0805USBC-TR |  | https://au.mouser.com/ProductDetail/Lumex/SML-LX0805USBC-TR?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 |  |  |  | SML-LX0805USBC-TR
22 | 2 | D43, D44 | LED (Orange) | Device:LED | LED_SMD:LED_0805_2012Metric_Pad1.15x1.40mm_HandSolder | ~ |  |  |  |  |  |  | AMS OSRAM | 720-LOR976-PS-1 |  | https://au.mouser.com/ProductDetail/ams-OSRAM/LO-R976-PS-1-0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 |  |  |  | LO R976-PS-1-0-20-R18
23 | 1 | F1 | Polyfuse 1A | Device:Polyfuse | Fuse:Fuse_2920_7451Metric_Castellated | ~ |  |  |  |  |  |  | Littelfuse | 530-0ZCF0100AF2A |  | https://au.mouser.com/ProductDetail/Bel-Fuse/0ZCF0100AF2A?qs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 |  |  |  | 0ZCF0100AF2A
24 | 13 | F2, F3, F4, F5, F6, F7, F8, F9, F10, F11, F12, F13, F14 | Fuse | Device:Fuse | Fuse:Fuse_0805_2012Metric_Pad1.15x1.40mm_HandSolder | ~ |  |  |  |  |  |  | Vishay | 594-MFU0805FF04000P1 |  | https://au.mouser.com/ProductDetail/Vishay-Beyschlag/MFU0805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 |  |  |  | MFU0805FF04000P100
25 | 1 | FB1 | Ferrite Bead | Device:FerriteBead | Inductor_SMD:L_0603_1608Metric_Pad1.05x0.95mm_HandSolder | ~ |  |  |  |  |  |  | TDK | 810-MMZ0603S102HT000 |  | https://au.mouser.com/ProductDetail/TDK/MMZ0603S102HT000?qs=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 |  |  |  | MMZ0603S102HT000
26 | 1 | IC1 | ADS7038QRTERQ1 | SamacSys_Parts:ADS7038QRTERQ1 | QFN50P300X300X80-17N-D | https://www.ti.com/lit/ds/symlink/ads7038-q1.pdf?ts=16095024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 |  | ADS7038 Q1 Small 8 Channel 12 Bit ADC With SPI Interface and CRC | 0.8 |  |  |  | Texas Instruments | NOT AVAILABLE! | https://www.mouser.co.uk/ProductDetail/Texas-Instruments/ADS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 | NOT AVAILABLE! |  |  |  | ADS7038QRTERQ1
27 | 2 | J1, J2 | Conn_02x03_Odd_Even | Connector_Generic:Conn_02x03_Odd_Even | Connector_Molex:Molex_Mini-Fit_Jr_5566-06A_2x03_P4.20mm_Vertical | ~ |  |  |  |  |  |  |  |  |  |  |  |  |  | -
28 | 1 | J3 | Conn_02x08_Odd_Even | Connector_Generic:Conn_02x08_Odd_Even |  | ~ |  |  |  |  |  |  |  |  |  |  |  |  |  | -
29 | 1 | J4 | Conn_01x13 | Connector_Generic:Conn_01x13 |  | ~ |  |  |  |  |  |  |  |  |  |  |  |  |  | -
30 | 3 | J5, J6, J12 | Conn_01x03 | Connector_Generic:Conn_01x03 | Connector_PinHeader_2.54mm:PinHeader_1x03_P2.54mm_Vertical | ~ |  |  |  |  |  |  |  |  |  |  |  |  |  | -
31 | 4 | J7, J8, J9, J10 | Conn_01x02 | Connector_Generic:Conn_01x02 | Connector_PinHeader_2.54mm:PinHeader_1x02_P2.54mm_Vertical | ~ |  |  |  |  |  |  |  |  |  |  |  |  |  | -
32 | 1 | J11 | Conn_ARM_JTAG_SWD_10 | Connector:Conn_ARM_JTAG_SWD_10 | Connector_PinHeader_1.27mm:PinHeader_2x09_P1.27mm_Vertical_SMD | http://infocenter.arm.com/help/topic/com.arm.doc.ddi0314h/DD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
33 | 1 | K1 | G5V-2 | Relay:G5V-2 | Relay_THT:Relay_DPDT_Omron_G5V-2 | http://omronfs.omron.com/en_US/ecb/products/pdf/en-g5v_2.pdf |  |  |  |  |  |  | Omron | 653-G5V-2-H1-DC12 |  | https://au.mouser.com/ProductDetail/Omron-Electronics/G5V-2-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 |  |  |  | G5V-2-H1-DC12
34 | 1 | L1 | 744272121 | Device:L_Ferrite_Coupled | Inductor_SMD:L_CommonModeChoke_Wuerth_WE-SL5 | ~ |  |  |  |  |  |  | Wurth | 710-744272121 |  | https://au.mouser.com/ProductDetail/Wurth-Elektronik/7442721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 |  |  |  | 744272121
35 | 1 | L2 | 0ZCF0100AF2A | Device:L_Ferrite_Coupled | Inductor_SMD:L_CommonModeChoke_Coilcraft_1812CAN | ~ |  |  |  |  |  |  | EPCOS - TDK | 871-B82787C104H2 |  | https://au.mouser.com/ProductDetail/EPCOS-TDK/B82787C0104H00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 |  |  |  | B82787C0104H002
36 | 1 | PS1 | R2S-053.3 | R2S-053.3:R2S-053.3 | CONV_R2S-053.3 |  |  |  |  | RECOM | 9.0mm |  | RECOM | 919-R2S-053.3 |  | https://au.mouser.com/ProductDetail/RECOM-Power/R2S-0533?qs=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 |  | 0 |  | 919-R2S-053.3 |  | Manufacturer Recommendations
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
